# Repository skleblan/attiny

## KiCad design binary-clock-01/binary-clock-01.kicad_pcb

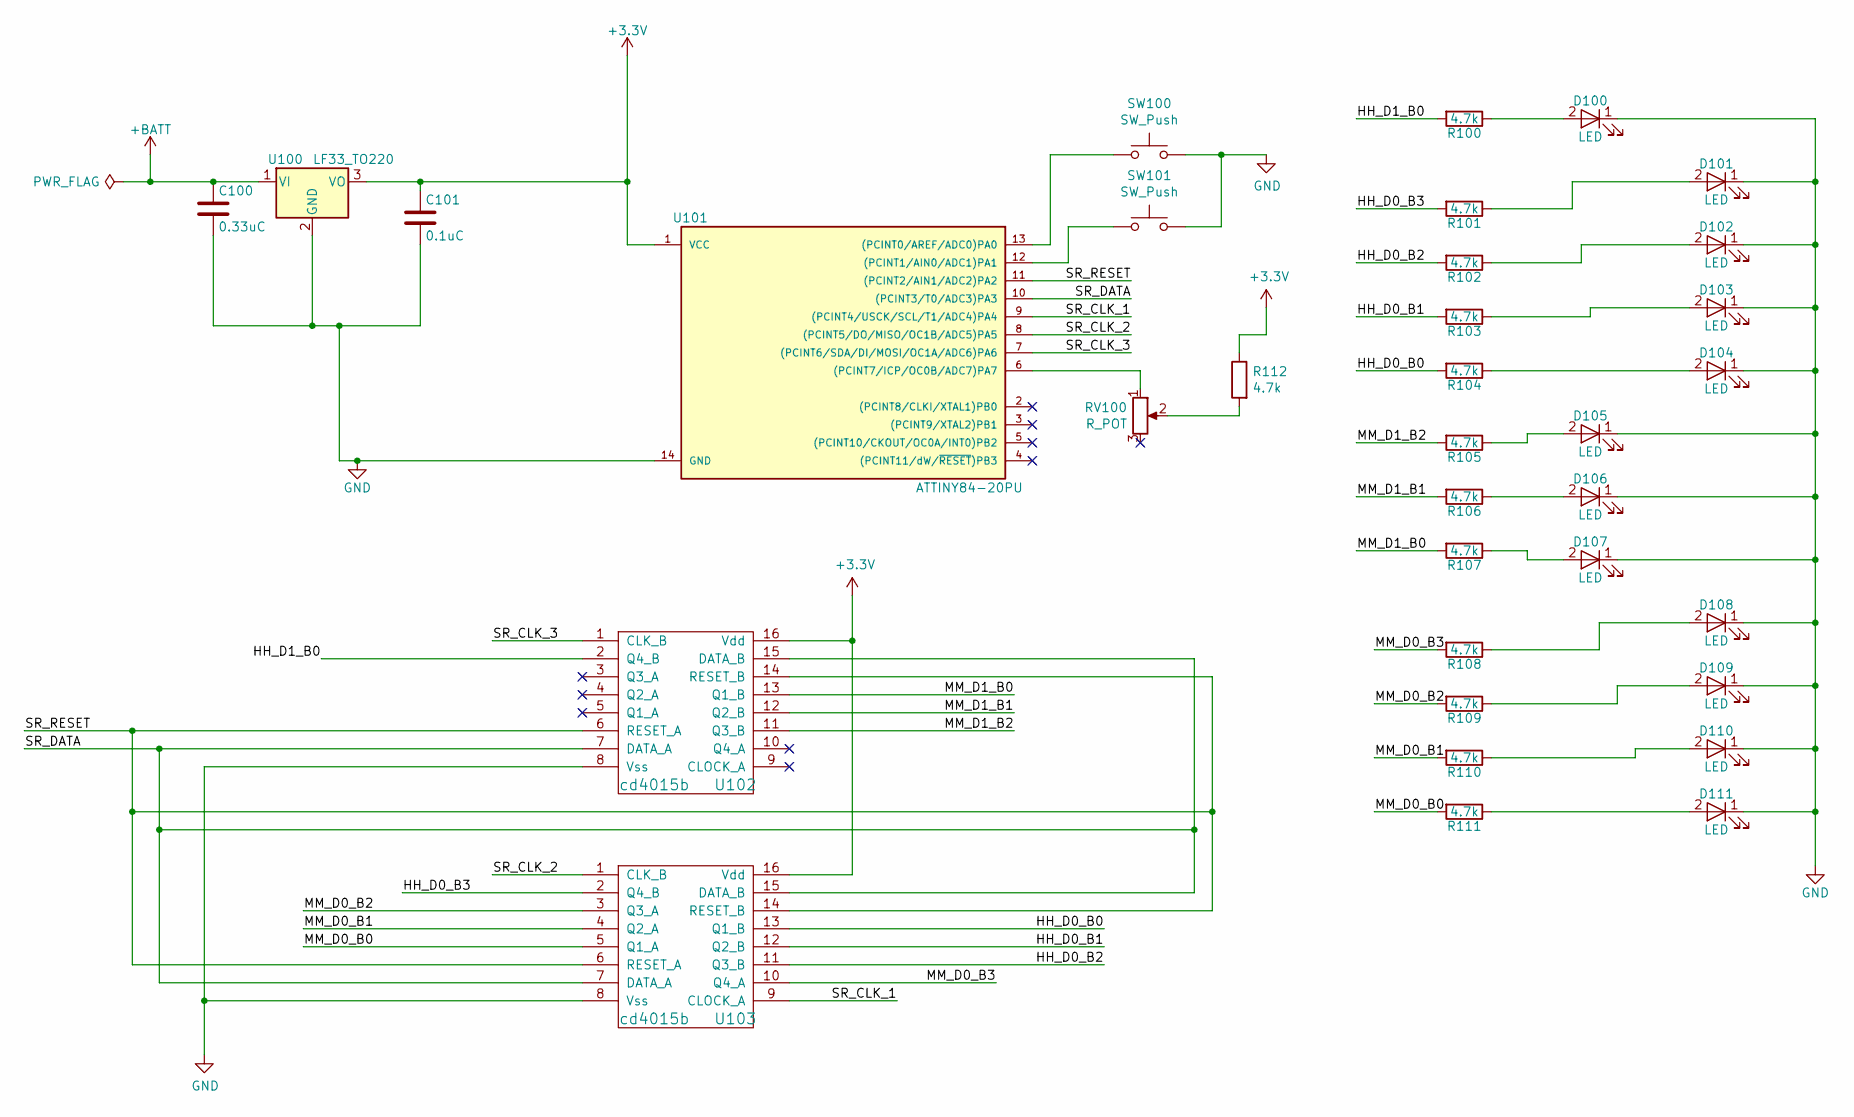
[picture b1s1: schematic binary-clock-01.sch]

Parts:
C100: 0.33uC; C_Radial_D6.3mm_H5.0mm_P2.50mm
C101: 0.1uC; C_Radial_D6.3mm_H5.0mm_P2.50mm
D100, D101, D102, D103, D104, D105, D106, D107, D108, D109, D110, D111: LED; LED_D5.0mm
R100, R101, R102, R103, R104, R105, R106, R107, R108, R109, R110, R111, R112: 4.7k; R_Axial_DIN0309_L9.0mm_D3.2mm_P12.70mm_Horizontal
RV100: R_POT; Potentiometer_Alps_RK09L_Single_Vertical
SW100, SW101: SW_Push; SW_PUSH_6mm
U100: LF33_TO220; ua78m33
U101: ATTINY84-20PU; ATTINY84-PDIP
U102, U103: cd4015b

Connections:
+3V3: C101.1, R112.1, U100.3 (VO), U101.1 (VCC), U102.16 (Vdd), U103.16 (Vdd)
+BATT: C100.1, U100.1 (VI)
/HH_D0_B0: R104.2, U103.13 (Q1_B)
/HH_D0_B1: R103.2, U103.12 (Q2_B)
/HH_D0_B2: R102.2, U103.11 (Q3_B)
/HH_D0_B3: R101.2, U103.2 (Q4_B)
/HH_D1_B0: R100.2, U102.2 (Q4_B)
/MM_D0_B0: R111.2, U103.5 (Q1_A)
/MM_D0_B1: R110.2, U103.4 (Q2_A)
/MM_D0_B2: R109.2, U103.3 (Q3_A)
/MM_D0_B3: R108.2, U103.10 (Q4_A)
/MM_D1_B0: R107.2, U102.13 (Q1_B)
/MM_D1_B1: R106.2, U102.12 (Q2_B)
/MM_D1_B2: R105.2, U102.11 (Q3_B)
/SR_CLK_1: U101.9 ((PCINT4/USCK/SCL/T1/ADC4)PA4), U103.9 (CLOCK_A)
/SR_CLK_2: U101.8 ((PCINT5/DO/MISO/OC1B/ADC5)PA5), U103.1 (CLK_B)
/SR_CLK_3: U101.7 ((PCINT6/SDA/DI/MOSI/OC1A/ADC6)PA6), U102.1 (CLK_B)
/SR_DATA: U101.10 ((PCINT3/T0/ADC3)PA3), U102.7 (DATA_A), U102.15 (DATA_B), U103.7 (DATA_A), U103.15 (DATA_B)
/SR_RESET: U101.11 ((PCINT2/AIN1/ADC2)PA2), U102.6 (RESET_A), U102.14 (RESET_B), U103.6 (RESET_A), U103.14 (RESET_B)
GND: C100.2, C101.2, D100.1 (K), D101.1 (K), D102.1 (K), D103.1 (K), D104.1 (K), D105.1 (K), D106.1 (K), D107.1 (K), D108.1 (K), D109.1 (K), D110.1 (K), D111.1 (K), SW100.2, SW101.2, U100.2 (GND), U101.14 (GND), U102.8 (Vss), U103.8 (Vss)
unnamed: D100.2 (A), R100.1
unnamed: D101.2 (A), R101.1
unnamed: D102.2 (A), R102.1
unnamed: D103.2 (A), R103.1
unnamed: D104.2 (A), R104.1
unnamed: D105.2 (A), R105.1
unnamed: D106.2 (A), R106.1
unnamed: D107.2 (A), R107.1
unnamed: D108.2 (A), R108.1
unnamed: D109.2 (A), R109.1
unnamed: D110.2 (A), R110.1
unnamed: D111.2 (A), R111.1
unnamed: R112.2, RV100.2
unnamed: RV100.1, U101.6 ((PCINT7/ICP/OC0B/ADC7)PA7)
unnamed: SW100.1, U101.13 ((PCINT0/AREF/ADC0)PA0)
unnamed: SW101.1, U101.12 ((PCINT1/AIN0/ADC1)PA1)

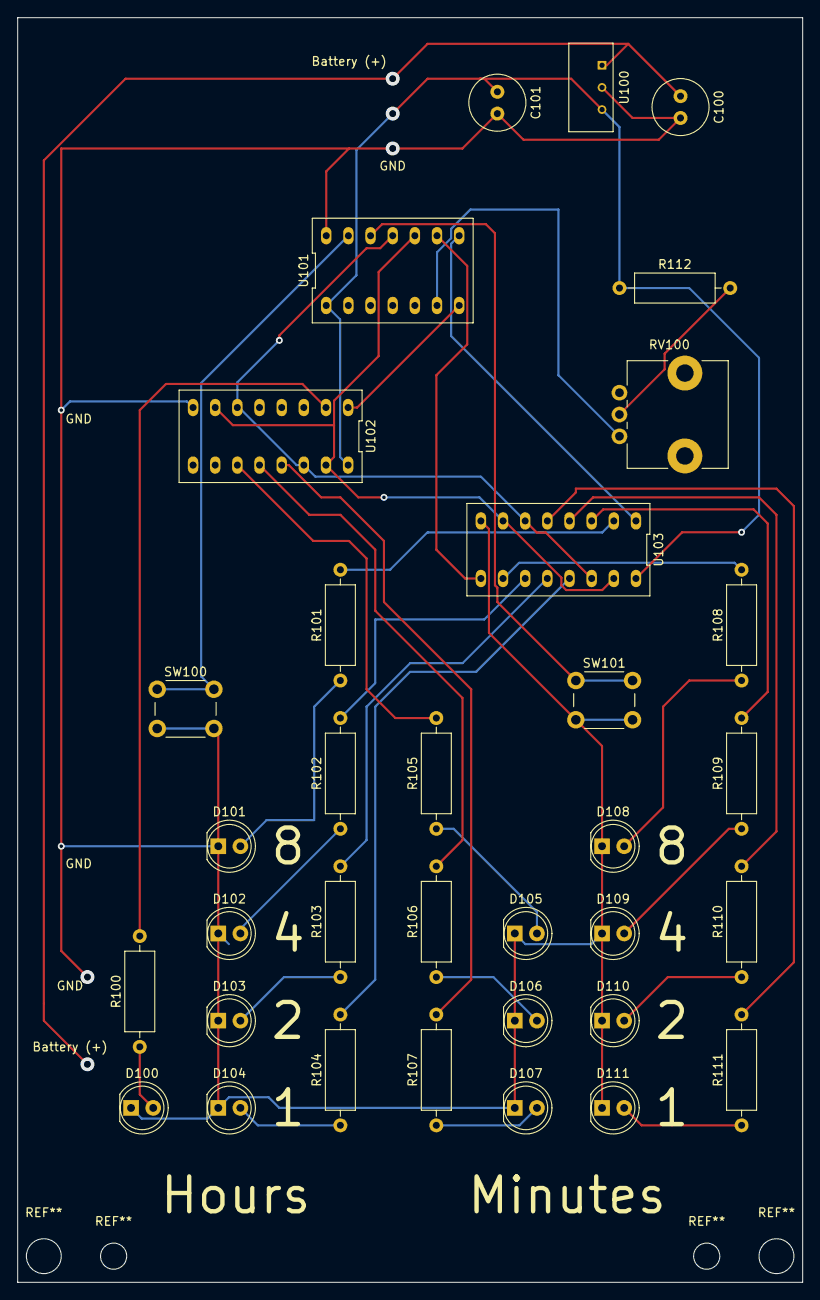
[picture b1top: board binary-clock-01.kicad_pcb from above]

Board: 2 copper layers, 90.0 x 145.0 mm, 34 parts (0 on the bottom side), 36 nets.

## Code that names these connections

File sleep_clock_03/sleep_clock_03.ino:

#include <avr/sleep.h>
#include <avr/interrupt.h>

//1024 prescaler
//using 1 MHz clock
//60,000,000 / 1024 = 58593.75 ticks
//65536-58594 = 6942 ticks remaining
int timer_reset = 6942;

int minutes = 0;
int hours = 12;

int hours_button = 13;
int minutes_button = 12;

int datapin = 10;
int minutes_ones_clkpin = 9;  //SR_CLK_1
int hours_ones_clkpin = 8;    //SR_CLK_2
int combined_tens_clkpin = 7; //SR_CLK_3
int resetpin = 11;

void setup() {
  pinMode(datapin, OUTPUT);
  pinMode(minutes_ones_clkpin, OUTPUT);
  pinMode(hours_ones_clkpin, OUTPUT);
  pinMode(combined_tens_clkpin, OUTPUT);
  pinMode(resetpin, OUTPUT);

//  pinMode(hours_button, INPUT);
//  pinMode(minutes_button, INPUT);

  cli();
  TCCR1A = 0;
  TCCR1B = 0;

  TCNT1 = timer_reset;
  TCCR1B |= (1 << CS12) | (1 << CS10); //1024 prescaler
  TIMSK1 |= (1 << TOIE1); //enable timer overflow interrupt
  sei();
}

ISR(TIM1_OVF_vect)
{
  TCNT1 = timer_reset; //reload initial value
  cli();
}

void skl_sleep()
{
  set_sleep_mode(SLEEP_MODE_IDLE);
  
  sleep_enable();
  sei();
  sleep_cpu();
  sleep_disable();
}

void sendbit(int clockpin, int val)
{
  digitalWrite(clockpin, LOW);
  digitalWrite(datapin, val);
  digitalWrite(clockpin, HIGH);
}

void sendfourbits(int pin, int val)
{
  int i;
  int curval;
  for(i = 0; i < 4; i++)
  {
    curval = (val >> i) & 0x1;
    sendbit(pin, curval);
  }
}

void clock_tick()
{
  minutes++;
  if(minutes > 59)
  {
    minutes = 0;
    hours++;
    if(hours > 12)
    {
      hours = 1;
    }
  }
}

void loop() {
  int combined_tens = 0;
  
  while(1)
  {
    clock_tick();

    sendfourbits( minutes_ones_clkpin, (minutes % 10) );
    sendfourbits( hours_ones_clkpin, (hours % 10) );

    combined_tens = ((hours/10)<<3) | ((minutes/10)<<0);
    sendfourbits( combined_tens_clkpin, combined_tens);

    skl_sleep();
  }
}

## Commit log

2020-10-27 allhigh and alllow
    two simple programs. one sets all digital I/O to high, the other sets
    all digital I/O to low.
    started work on a blinky program. unfinished
2020-10-27 added gitignore
2020-10-29 build scripts
2020-10-29 Alternative blinky. alt allhigh. unsuccessful
2020-11-03 POC. 4bit second timer
    Proof of Concepts.
    Successfully programmed attiny with blinky code
    and with the 4bit second timer.
2020-11-20 sample arduino sketch. seconds counter
    Sample arduino sketch. predecessor for binary clock.
    increments every second. 4 bits. uses built-in delay() function.
    includes using one of the shift registors.
    software ran successfully on collection of breadboards
2020-11-20 ki-cad project.
    need more comments
    custom components created
    custom footprints created
    schematic done
    working on layout
2021-02-02 finish pcb layout
2021-02-02 several proof-of-concepts
    shift register project
    clock timer via interrupt
    clock timer via interrupt w/ low power mode
    button isr
2021-02-02 index notes for each of the diff arduino projs
    properties
    - name
    - status (success, failure, incomplete, unknown)
    - various experimental features (timer/button isr, low pwr, shift reg)
    - final output seen by user
2021-02-02 Final SW for binary clock. unofficial v1.
    Started work on final software for binary clock. Partial success.
    See notes.txt for list of accomplishments and improvements.
    Improvements will be made in same arduino project.
2021-02-04 Edge-detection experiments
    Trying to work on code to detect edges (rising/falling) of button
    presses. Having issues w/ parasitics. Are we sure that the
    internal pull up resistors are working correctly?
2021-02-04 Successful edge detection
    pins were configured incorrectly during my proof-of-concept
    experimenting.
    Ported code back to final project and working as intended.
2021-02-05 watchdog experiments
    ran 2 experiments using the watchdog as a timer
    one was at full power, and one was sleeping in between w/ the watchdog
    generating interrupts
    made some rough current measurements and wrote them down
2021-02-21 Watchdog integration on PCB
    Currently failing. not sure what went wrong.
    1's digit keeps blinking every second in minutes
    minutes do not change otherwise
    hours get's stuck at 12, if i time the hours-btn press right
    it might get advanced to 1, but then things reset
